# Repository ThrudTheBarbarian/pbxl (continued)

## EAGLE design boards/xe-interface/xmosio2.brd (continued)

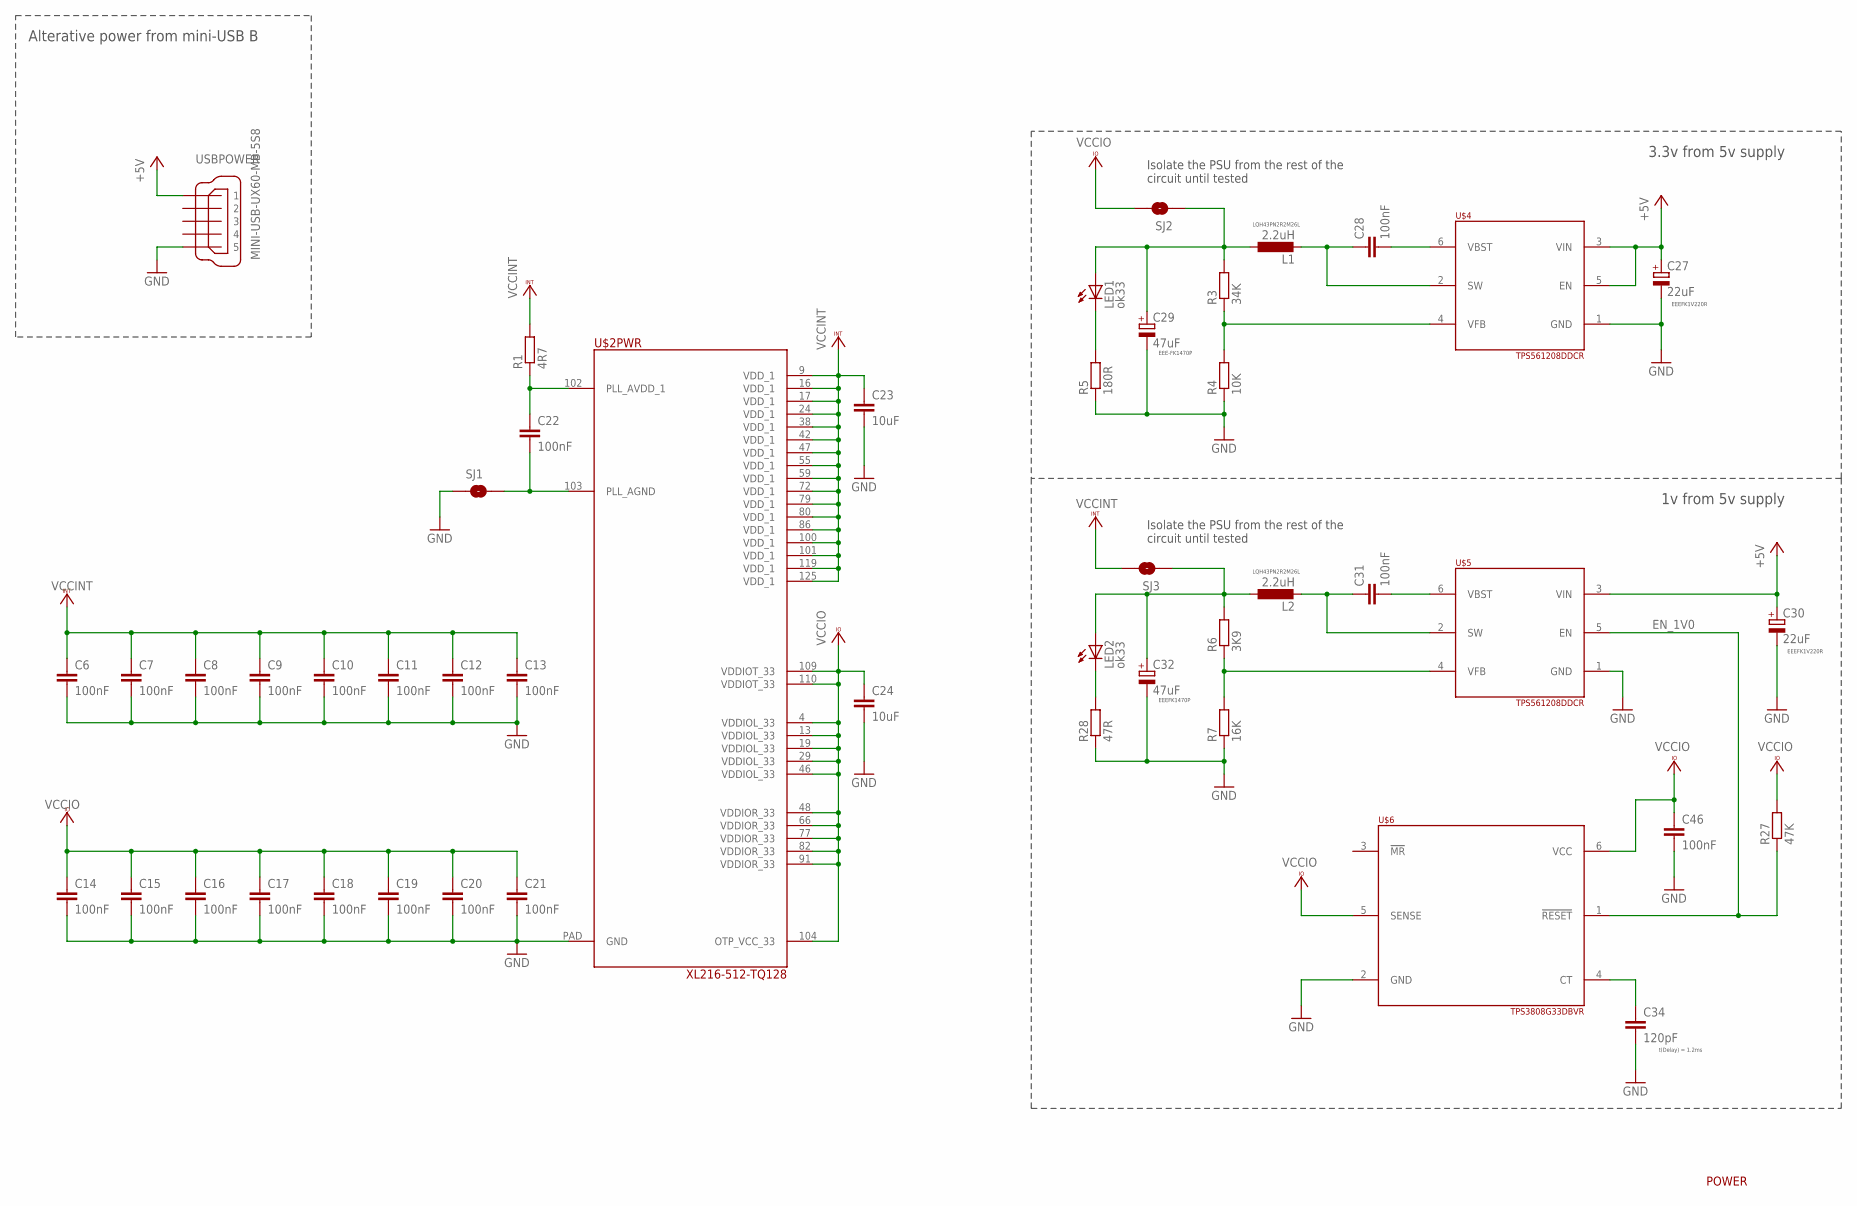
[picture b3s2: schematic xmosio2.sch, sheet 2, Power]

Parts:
C6, C7, C8, C9, C10, C11, C12, C13, C14, C15, C16, C17, C18, C19, C20, C21, C22, C28, C31, C46: 100nF; C1206
C23, C24: 10uF; C1206
C27, C30: 22uF; PANASONIC_C
C29, C32: 47uF; PANASONIC_D
C34: 120pF; C1206
L1, L2: 2.2uH; L1812
LED1, LED2: ok33; CHIP-LED0805
R1: 4R7; R1206
R3: 34K; R1206
R4: 10K; R1206
R5: 180R; R1206
R6: 3K9; R1206
R7: 16K; R1206
R27: 47K; R1206
R28: 47R; R1206
SJ1: SOLDERJUMPERNC; SJ_2S
SJ2, SJ3: SOLDERJUMPERNO; SJ_2S-NO
U$2: XL216-512-TQ128; TQFP128
U$4, U$5: TPS561208DDCR; TSOT23-6_DDC
U$6: TPS3808G33DBVR; SOT23-6
USBPOWER: MINI-USB-UX60-MB-5S8; UX60-MB-5S8

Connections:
+5V: C27.+, C30.+, U$4.3 (VIN), U$4.5 (EN), U$5.3 (VIN), USBPOWER.1; also elsewhere on the board
EN_1V0: R27.1, U$5.5 (EN), U$6.1 (!RESET!)
GND: C6.2, C7.2, C8.2, C9.2, C10.2, C11.2, C12.2, C13.2, C14.2, C15.2, C16.2, C17.2, C18.2, C19.2, C20.2, C21.2, C23.2, C24.2, C27.-, C29.-, C30.-, C32.-, C34.2, C46.2, R4.1, R5.1, R7.1, R28.1, SJ1.1, U$2.PAD (GND), U$4.1 (GND), U$5.1 (GND), U$6.2 (GND), USBPOWER.5; also elsewhere on the board
unnamed: C22.1, R1.1, U$2.102 (PLL_AVDD_1)
unnamed: C22.2, SJ1.2, U$2.103 (PLL_AGND)
unnamed: C28.2, U$4.6 (VBST)
unnamed: C28.1, L1.2, U$4.2 (SW)
unnamed: C31.2, U$5.6 (VBST)
unnamed: R3.1, R4.2, U$4.4 (VFB)
unnamed: LED1.C, R5.2
unnamed: C31.1, L2.2, U$5.2 (SW)
unnamed: R6.1, R7.2, U$5.4 (VFB)
unnamed: C34.1, U$6.4 (CT)
unnamed: C29.+, L1.1, LED1.A, R3.2, SJ2.1
unnamed: LED2.C, R28.2
unnamed: C32.+, L2.1, LED2.A, R6.2, SJ3.1
VCCINT: C6.1, C7.1, C8.1, C9.1, C10.1, C11.1, C12.1, C13.1, C23.1, R1.2, SJ3.2, U$2.9 (VDD_1), U$2.16 (VDD_1), U$2.17 (VDD_1), U$2.24 (VDD_1), U$2.38 (VDD_1), U$2.42 (VDD_1), U$2.47 (VDD_1), U$2.55 (VDD_1), U$2.59 (VDD_1), U$2.72 (VDD_1), U$2.79 (VDD_1), U$2.80 (VDD_1), U$2.86 (VDD_1), U$2.100 (VDD_1), U$2.101 (VDD_1), U$2.119 (VDD_1), U$2.125 (VDD_1); also elsewhere on the board
VCCIO: C14.1, C15.1, C16.1, C17.1, C18.1, C19.1, C20.1, C21.1, C24.1, C46.1, R27.2, SJ2.2, U$2.4 (VDDIOL_33), U$2.13 (VDDIOL_33), U$2.19 (VDDIOL_33), U$2.29 (VDDIOL_33), U$2.46 (VDDIOL_33), U$2.48 (VDDIOR_33), U$2.66 (VDDIOR_33), U$2.77 (VDDIOR_33), U$2.82 (VDDIOR_33), U$2.91 (VDDIOR_33), U$2.104 (OTP_VCC_33), U$2.109 (VDDIOT_33), U$2.110 (VDDIOT_33), U$6.5 (SENSE), U$6.6 (VCC); also elsewhere on the board

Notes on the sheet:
EEEFK1V220R
LQH43PN2R2M26L
EEE-FK1470P
3.3v from 5v supply
EEEFK1470P
1v from 5v supply
t(Delay) = 1.2ms
POWER
Alterative power from mini-USB B
Isolate the PSU from the rest of the circuit until tested

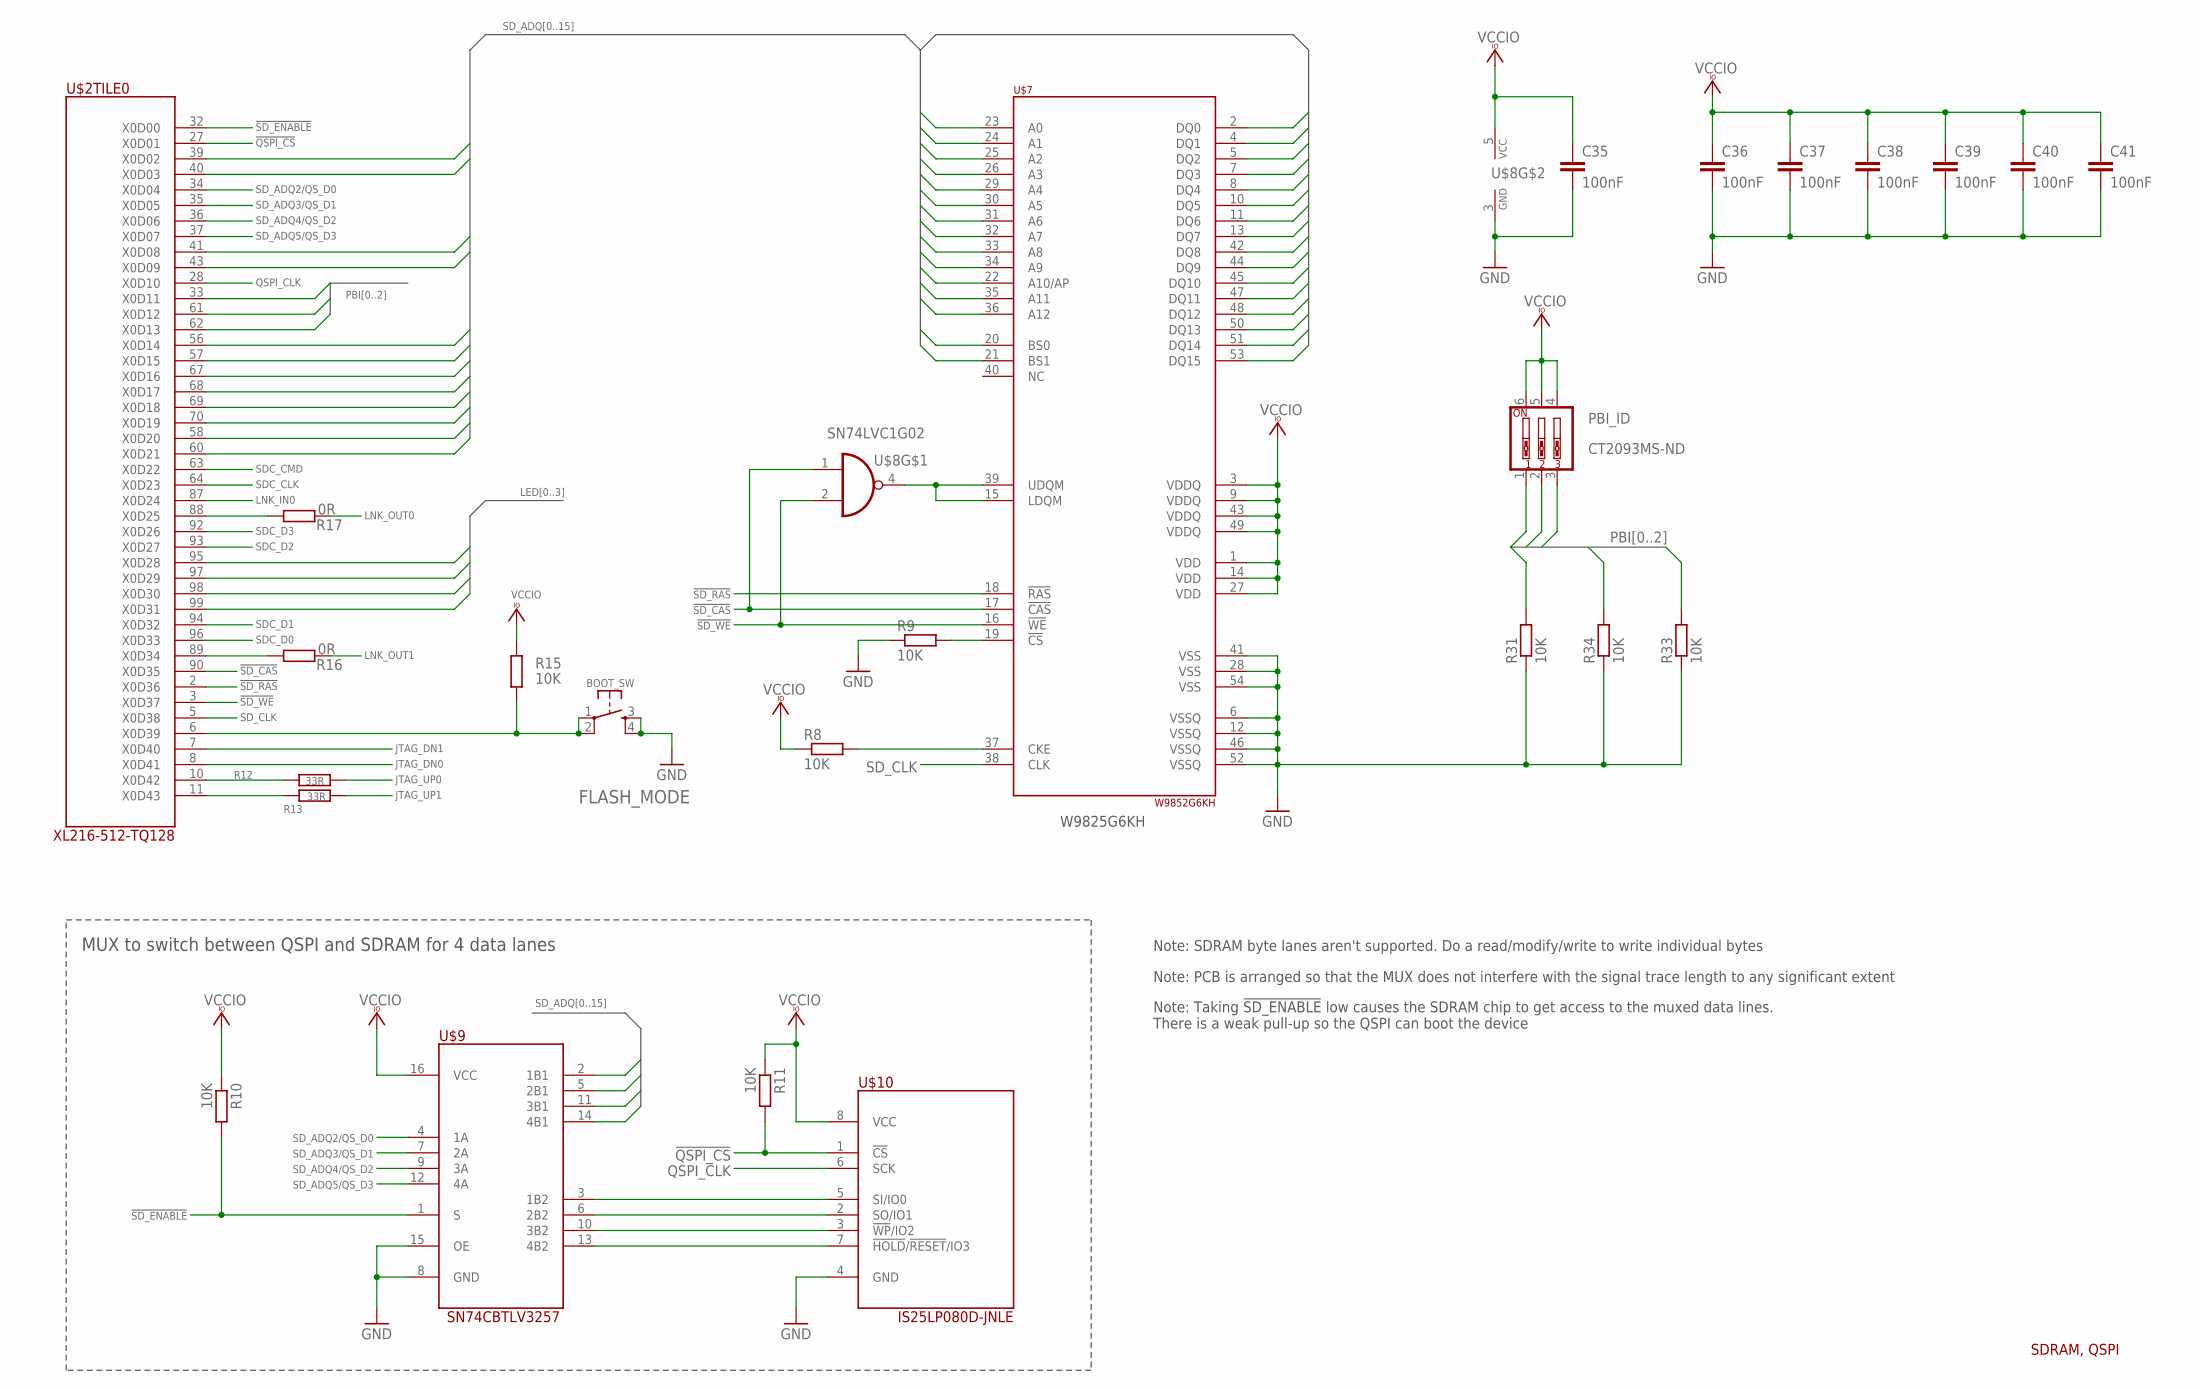
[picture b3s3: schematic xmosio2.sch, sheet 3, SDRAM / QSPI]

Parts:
BOOT_SW: FLASH_MODE; TACTILE-PTH
C35, C36, C37, C38, C39, C40, C41: 100nF; C1206
PBI_ID: CT2093MS-ND; EDG-03
R8, R9, R10, R11, R15, R31, R33, R34: 10K; R1206
R12, R13: 33R; R1206
R16, R17: 0R; R1206
U$2: XL216-512-TQ128; TQFP128
U$7: W9852G6KH; TSOP54-400
U$8: SN74LVC1G02; SOT23-5
U$9: SN74CBTLV3257; SO16
U$10: IS25LP080D-JNLE; SO-08

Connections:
!QSPI_CS!: R11.2, U$2.27 (X0D01), U$10.1 (!CS!)
!SD_CAS!: U$2.90 (X0D35), U$7.17 (!CAS!), U$8.1 (I0)
!SD_ENABLE!: R10.2, U$2.32 (X0D00), U$9.1 (S)
!SD_RAS!: U$2.2 (X0D36), U$7.18 (!RAS!)
!SD_WE!: U$2.3 (X0D37), U$7.16 (!WE!), U$8.2 (I1)
GND: BOOT_SW.3, BOOT_SW.4, C35.2, C36.2, C37.2, C38.2, C39.2, C40.2, C41.2, R9.1, R31.1, R33.1, R34.1, U$7.6 (VSSQ), U$7.12 (VSSQ), U$7.28 (VSS), U$7.41 (VSS), U$7.46 (VSSQ), U$7.52 (VSSQ), U$7.54 (VSS), U$8.3 (GND), U$9.8 (GND), U$9.15 (OE), U$10.4 (GND); also elsewhere on the board
JTAG_DN0: U$2.8 (X0D41); also elsewhere on the board
JTAG_DN1: U$2.7 (X0D40); also elsewhere on the board
JTAG_UP0: R12.2; also elsewhere on the board
JTAG_UP1: R13.2; also elsewhere on the board
LED0: U$2.95 (X0D28); also elsewhere on the board
LED1: U$2.97 (X0D29); also elsewhere on the board
LED2: U$2.98 (X0D30); also elsewhere on the board
LED3: U$2.99 (X0D31); also elsewhere on the board
LNK_IN0: U$2.87 (X0D24); also elsewhere on the board
LNK_OUT0: R17.2; also elsewhere on the board
LNK_OUT1: R16.2; also elsewhere on the board
unnamed: U$7.15 (LDQM), U$7.39 (UDQM), U$8.4 (O)
unnamed: R8.2, U$7.37 (CKE)
unnamed: U$9.3 (1B2), U$10.5 (SI/IO0)
unnamed: R9.2, U$7.19 (!CS!)
unnamed: U$9.6 (2B2), U$10.2 (SO/IO1)
unnamed: U$9.10 (3B2), U$10.3 (!WP!/IO2)
unnamed: U$9.13 (4B2), U$10.7 (!HOLD!/!RESET!/IO3)
unnamed: R12.1, U$2.10 (X0D42)
unnamed: R13.1, U$2.11 (X0D43)
unnamed: R17.1, U$2.88 (X0D25)
unnamed: R16.1, U$2.89 (X0D34)
unnamed: BOOT_SW.1, BOOT_SW.2, R15.1, U$2.6 (X0D39)
PBI0: PBI_ID.1, R31.2, U$2.33 (X0D11)
PBI1: PBI_ID.2, R34.2, U$2.61 (X0D12)
PBI2: PBI_ID.3, R33.2, U$2.62 (X0D13)
QSPI_CLK: U$2.28 (X0D10), U$10.6 (SCK)
SDC_CLK: U$2.64 (X0D23); also elsewhere on the board
SDC_CMD: U$2.63 (X0D22); also elsewhere on the board
SDC_D0: U$2.96 (X0D33); also elsewhere on the board
SDC_D1: U$2.94 (X0D32); also elsewhere on the board
SDC_D2: U$2.93 (X0D27); also elsewhere on the board
SDC_D3: U$2.92 (X0D26); also elsewhere on the board
SD_ADQ0: U$2.39 (X0D02), U$7.2 (DQ0), U$7.23 (A0)
SD_ADQ1: U$2.40 (X0D03), U$7.4 (DQ1), U$7.24 (A1)
SD_ADQ2: U$7.5 (DQ2), U$7.25 (A2), U$9.2 (1B1)
SD_ADQ2/QS_D0: U$2.34 (X0D04), U$9.4 (1A)
SD_ADQ3: U$7.7 (DQ3), U$7.26 (A3), U$9.5 (2B1)
SD_ADQ3/QS_D1: U$2.35 (X0D05), U$9.7 (2A)
SD_ADQ4: U$7.8 (DQ4), U$7.29 (A4), U$9.11 (3B1)
SD_ADQ4/QS_D2: U$2.36 (X0D06), U$9.9 (3A)
SD_ADQ5: U$7.10 (DQ5), U$7.30 (A5), U$9.14 (4B1)
SD_ADQ5/QS_D3: U$2.37 (X0D07), U$9.12 (4A)
SD_ADQ6: U$2.41 (X0D08), U$7.11 (DQ6), U$7.31 (A6)
SD_ADQ7: U$2.43 (X0D09), U$7.13 (DQ7), U$7.32 (A7)
SD_ADQ8: U$2.56 (X0D14), U$7.33 (A8), U$7.42 (DQ8)
SD_ADQ9: U$2.57 (X0D15), U$7.34 (A9), U$7.44 (DQ9)
SD_ADQ10: U$2.67 (X0D16), U$7.22 (A10/AP), U$7.45 (DQ10)
SD_ADQ11: U$2.68 (X0D17), U$7.35 (A11), U$7.47 (DQ11)
SD_ADQ12: U$2.69 (X0D18), U$7.36 (A12), U$7.48 (DQ12)
SD_ADQ13: U$2.70 (X0D19), U$7.20 (BS0), U$7.50 (DQ13)
SD_ADQ14: U$2.58 (X0D20), U$7.21 (BS1), U$7.51 (DQ14)
SD_ADQ15: U$2.60 (X0D21), U$7.53 (DQ15)
SD_CLK: U$2.5 (X0D38), U$7.38 (CLK)
VCCIO: C35.1, C36.1, C37.1, C38.1, C39.1, C40.1, C41.1, PBI_ID.4, PBI_ID.5, PBI_ID.6, R8.1, R10.1, R11.1, R15.2, U$7.1 (VDD), U$7.3 (VDDQ), U$7.9 (VDDQ), U$7.14 (VDD), U$7.27 (VDD), U$7.43 (VDDQ), U$7.49 (VDDQ), U$8.5 (VCC), U$9.16 (VCC), U$10.8 (VCC); also elsewhere on the board

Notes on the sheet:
Note: Taking !SD_ENABLE! low causes the SDRAM chip to get access to the muxed data lines. There is a weak pull-up so the QSPI can boot the device
SDRAM, QSPI
MUX to switch between QSPI and SDRAM for 4 data lanes
Note: PCB is arranged so that the MUX does not interfere with the signal trace length to any significant extent
Note: SDRAM byte lanes aren't supported. Do a read/modify/write to write individual bytes
W9825G6KH

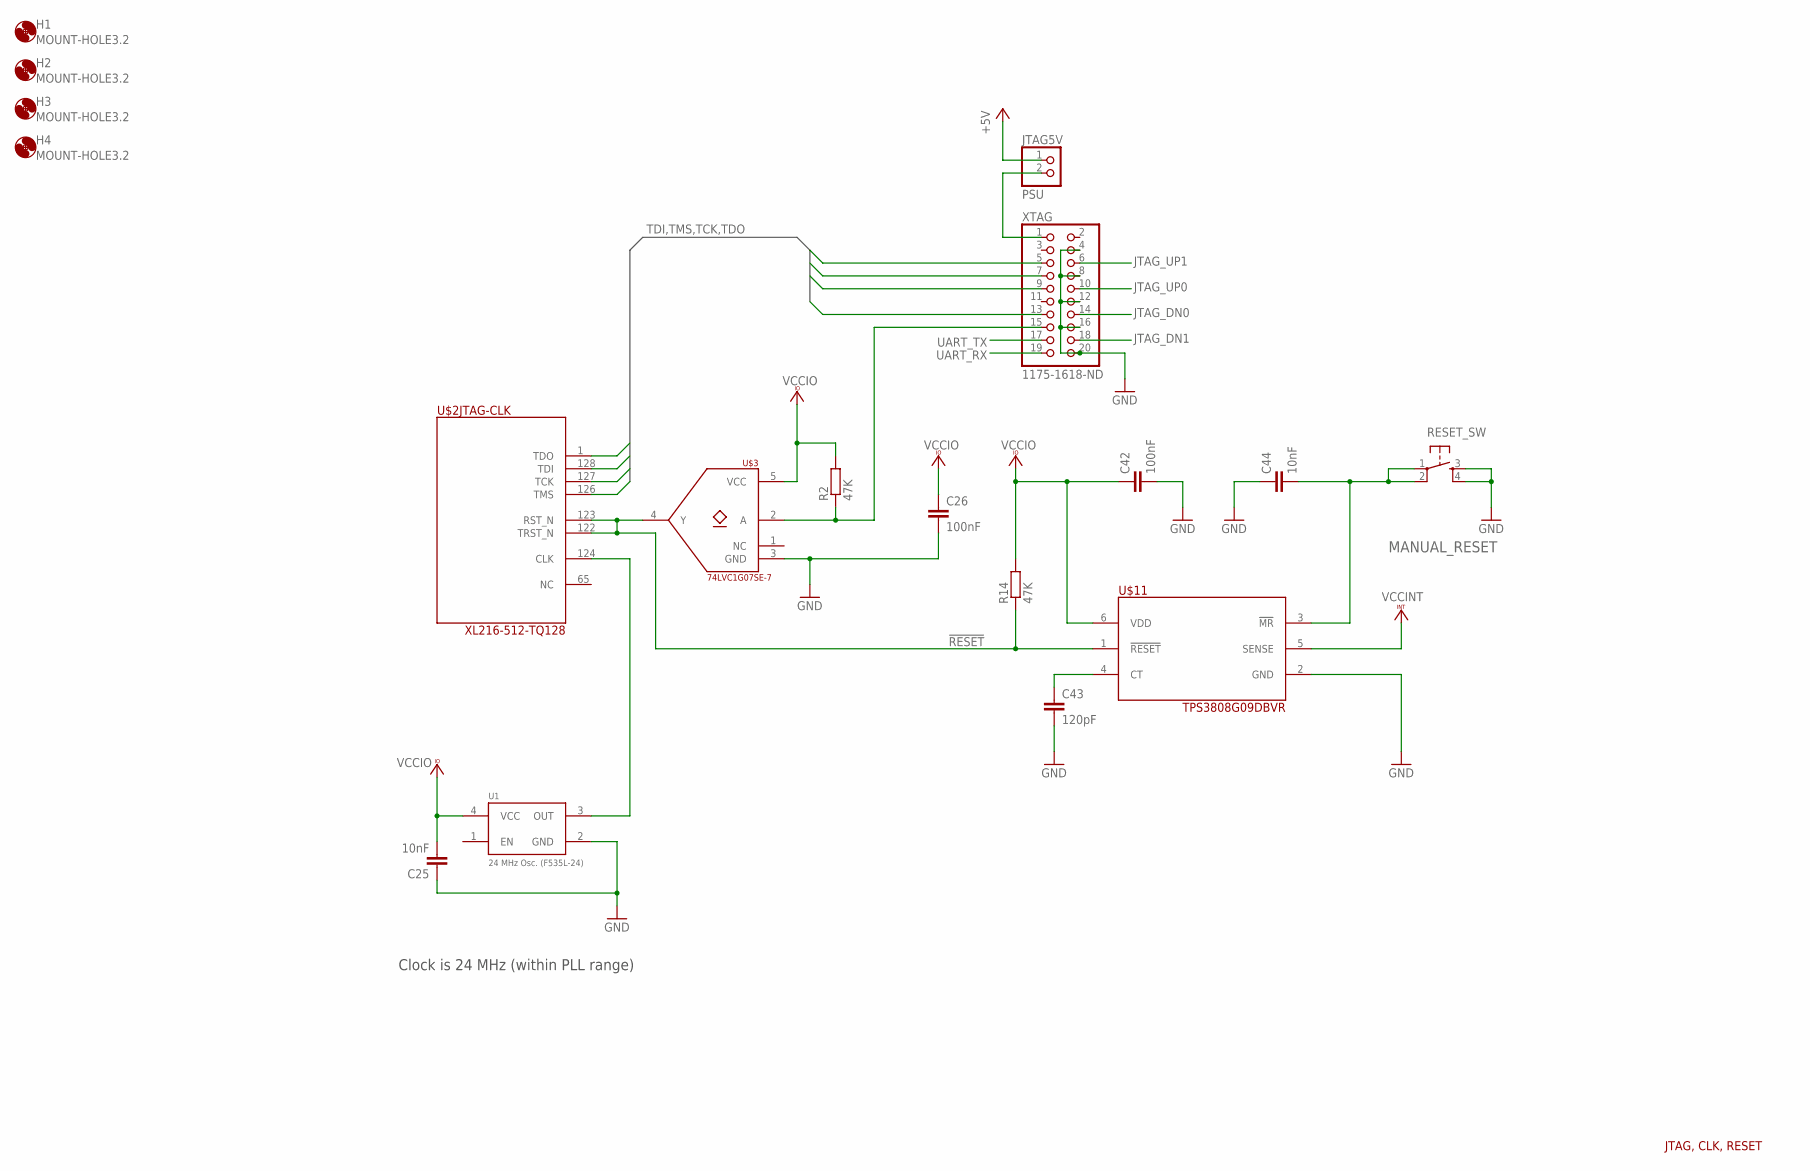
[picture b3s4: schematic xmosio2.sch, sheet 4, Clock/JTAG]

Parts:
C25, C44: 10nF; C1206
C26, C42: 100nF; C1206
C43: 120pF; C1206
H1, H2, H3, H4: MOUNT-HOLE3.2; 3,2
JTAG5V: PSU; 1X02
R2, R14: 47K; R1206
RESET_SW: MANUAL_RESET; TACTILE-PTH
U1: 24 MHz Osc. (F535L-24); CRYSTAL-OSC-SMD-5X3
U$2: XL216-512-TQ128; TQFP128
U$3: 74LVC1G07SE-7; SOT23-5
U$11: TPS3808G09DBVR; SOT23-6
XTAG: 1175-1618-ND; 2X10/90

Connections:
!RESET!: R14.1, U$2.122 (TRST_N), U$2.123 (RST_N), U$3.4 (Y), U$11.1 (!RESET!)
+5V: JTAG5V.1; also elsewhere on the board
GND: C25.1, C26.2, C42.2, C43.2, C44.1, RESET_SW.3, RESET_SW.4, U1.2 (GND), U$3.3 (GND), U$11.2 (GND), XTAG.4, XTAG.8, XTAG.12, XTAG.16, XTAG.20; also elsewhere on the board
JTAG_DN0: XTAG.14; also elsewhere on the board
JTAG_DN1: XTAG.18; also elsewhere on the board
JTAG_UP0: XTAG.10; also elsewhere on the board
JTAG_UP1: XTAG.6; also elsewhere on the board
unnamed: U1.3 (OUT), U$2.124 (CLK)
unnamed: R2.1, U$3.2 (A), XTAG.15
unnamed: C43.1, U$11.4 (CT)
unnamed: JTAG5V.2, XTAG.1
TCK: U$2.127 (TCK), XTAG.9
TDI: U$2.128 (TDI), XTAG.5
TDO: U$2.1 (TDO), XTAG.13
TMS: U$2.126 (TMS), XTAG.7
TRST_N: C44.2, RESET_SW.1, RESET_SW.2, U$11.3 (!MR!)
UART_RX: XTAG.19; also elsewhere on the board
UART_TX: XTAG.17; also elsewhere on the board
VCCINT: U$11.5 (SENSE); also elsewhere on the board
VCCIO: C25.2, C26.1, C42.1, R2.2, R14.2, U1.4 (VCC), U$3.5 (VCC), U$11.6 (VDD); also elsewhere on the board

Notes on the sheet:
JTAG, CLK, RESET
Clock is 24 MHz (within PLL range)

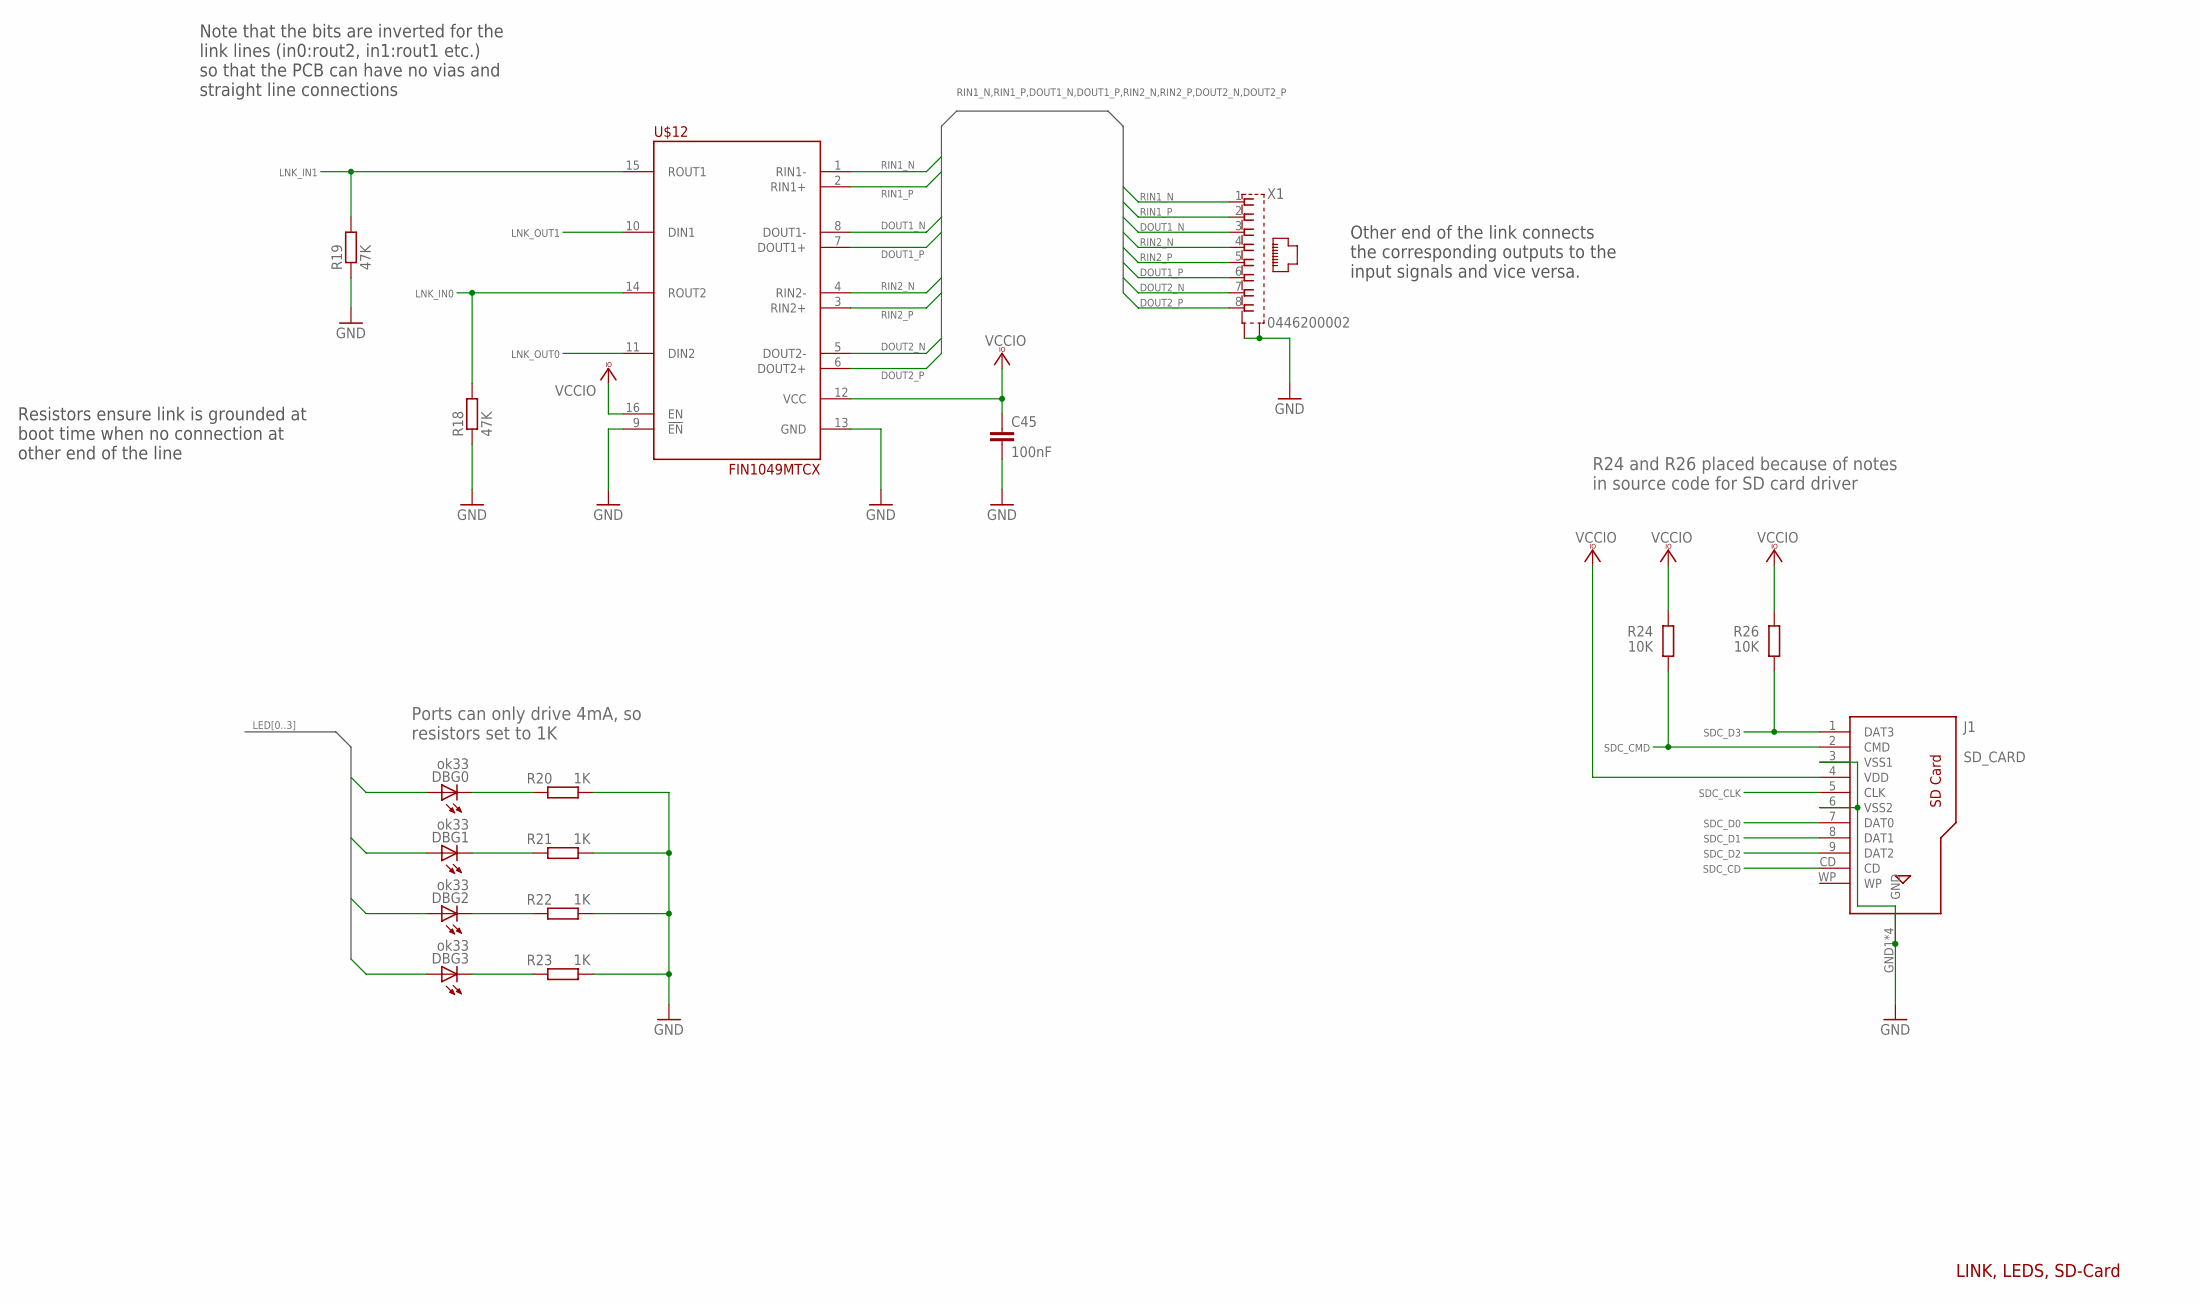
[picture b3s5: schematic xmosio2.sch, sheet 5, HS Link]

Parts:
C45: 100nF; C1206
DBG0, DBG1, DBG2, DBG3: ok33; CHIP-LED0805
J1: SD_CARD; 693063020911
R18, R19: 47K; R1206
R20, R21, R22, R23: 1K; R1206
R24, R26: 10K; R1206
U$12: FIN1049MTCX; TSSOP16
X1: 0446200002

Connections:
DOUT1_N: U$12.8 (DOUT1-), X1.3
DOUT1_P: U$12.7 (DOUT1+), X1.6
DOUT2_N: U$12.5 (DOUT2-), X1.7
DOUT2_P: U$12.6 (DOUT2+), X1.8
GND: C45.2, J1.3 (VSS1), J1.6 (VSS2), J1.GND1 (GND), J1.GND2 (GND), J1.GND3 (GND), J1.GND4 (GND), R18.1, R19.1, R20.2, R21.2, R22.2, R23.2, U$12.9 (!EN!), U$12.13 (GND), X1.S@1 (S1), X1.S@2 (S2); also elsewhere on the board
LED0: DBG0.A; also elsewhere on the board
LED1: DBG1.A; also elsewhere on the board
LED2: DBG2.A; also elsewhere on the board
LED3: DBG3.A; also elsewhere on the board
LNK_IN0: R18.2, U$12.14 (ROUT2); also elsewhere on the board
LNK_IN1: R19.2, U$12.15 (ROUT1); also elsewhere on the board
LNK_OUT0: U$12.11 (DIN2); also elsewhere on the board
LNK_OUT1: U$12.10 (DIN1); also elsewhere on the board
unnamed: DBG3.C, R23.1
unnamed: DBG2.C, R22.1
unnamed: DBG1.C, R21.1
unnamed: DBG0.C, R20.1
RIN1_N: U$12.1 (RIN1-), X1.1
RIN1_P: U$12.2 (RIN1+), X1.2
RIN2_N: U$12.4 (RIN2-), X1.4
RIN2_P: U$12.3 (RIN2+), X1.5
SDC_CD: J1.CD; also elsewhere on the board
SDC_CLK: J1.5 (CLK); also elsewhere on the board
SDC_CMD: J1.2 (CMD), R24.1; also elsewhere on the board
SDC_D0: J1.7 (DAT0); also elsewhere on the board
SDC_D1: J1.8 (DAT1); also elsewhere on the board
SDC_D2: J1.9 (DAT2); also elsewhere on the board
SDC_D3: J1.1 (DAT3), R26.2; also elsewhere on the board
VCCIO: C45.1, J1.4 (VDD), R24.2, R26.1, U$12.12 (VCC), U$12.16 (EN); also elsewhere on the board

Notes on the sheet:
Resistors ensure link is grounded at boot time when no connection at other end of the line
Note that the bits are inverted for the link lines (in0:rout2, in1:rout1 etc.) so that the PCB can have no vias and straight line connections
Other end of the link connects the corresponding outputs to the input signals and vice versa.
LINK, LEDS, SD-Card
Ports can only drive 4mA, so resistors set to 1K
R24 and R26 placed because of notes in source code for SD card driver

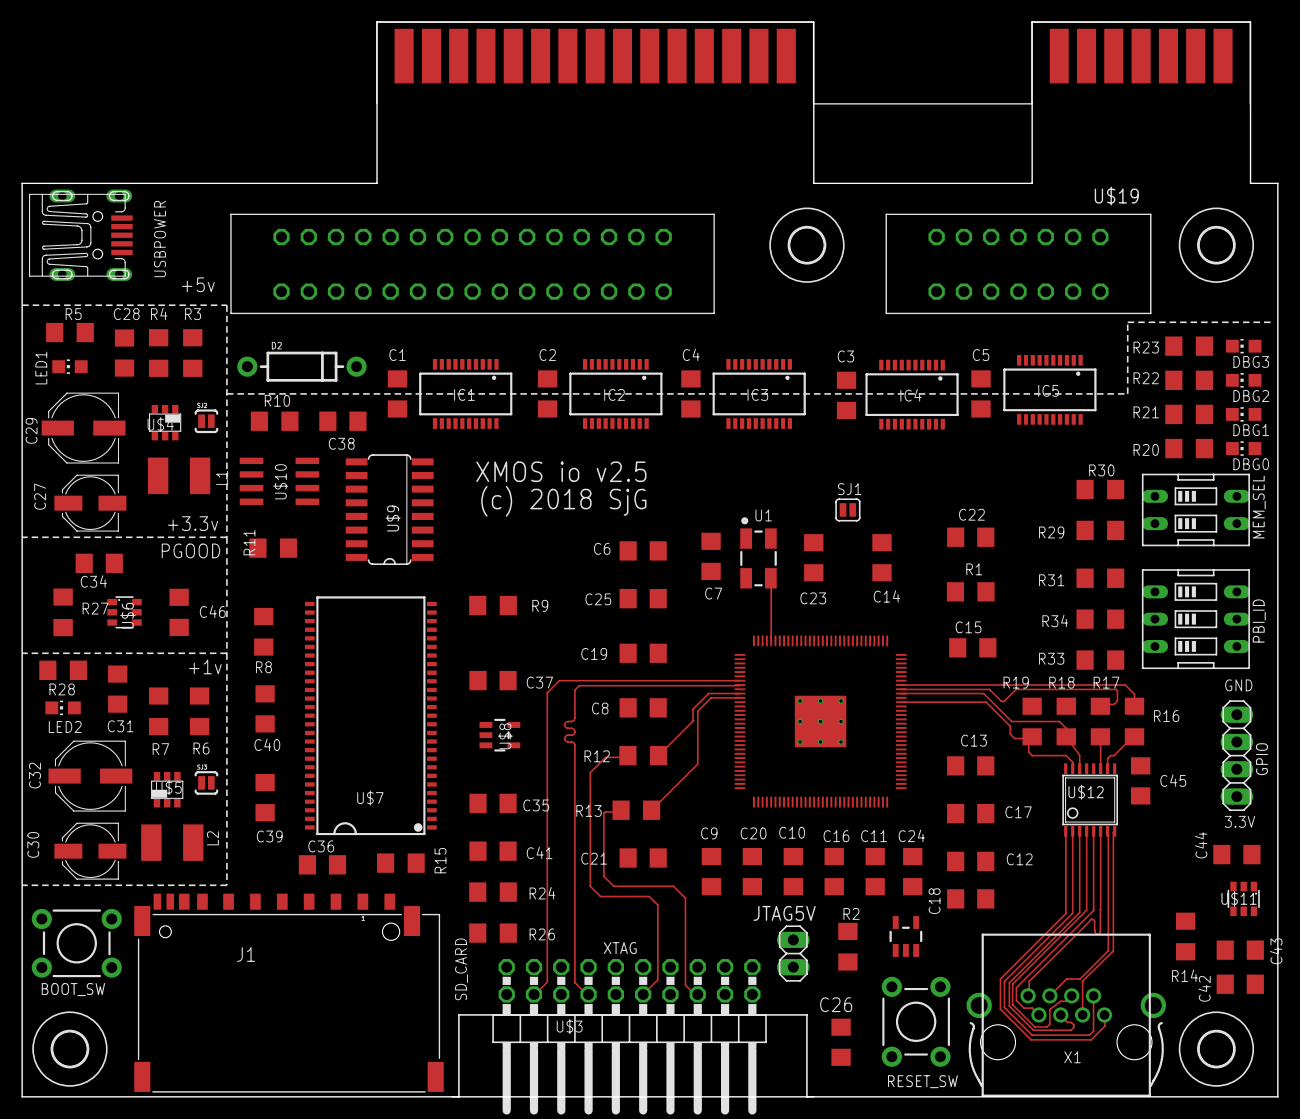
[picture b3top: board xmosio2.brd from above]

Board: 4 copper layers, 116.8 x 100.0 mm, 122 parts (0 on the bottom side), 182 nets.
